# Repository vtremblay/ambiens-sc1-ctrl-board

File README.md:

# ambiens-sc1-ctrl-board

The Ambiens SC1 Control Board is the heart of a smart heated 3D printer chamber designed to create an optimal environment for 3D printing by precisely controlling temperature and air quality. It continuously monitors the air quality inside the chamber using two BME680 sensors to assess the Indoor Air Quality (IAQ). Depending on the IAQ levels, a PWM fan is activated, working in conjunction with a HEPA filter and activated charcoal filters to purify the air.

To maintain the ideal temperature for different printing materials, the chamber utilizes a generic 12V PTC heater (120W) paired with a fan. The system's safety is enhanced by a 100k NTC sensor embedded in the PTC heater to monitor its internal temperature, alongside a thermal fuse to prevent overheating by automatically cutting off the heater if temperatures exceed safe levels.

The control board is powered by an ATX PSU and interfaces with a Raspberry Pi 3B via I2C, offering a smart, modular solution for 3D printing enthusiasts looking to optimize their printing environment for quality and safety.

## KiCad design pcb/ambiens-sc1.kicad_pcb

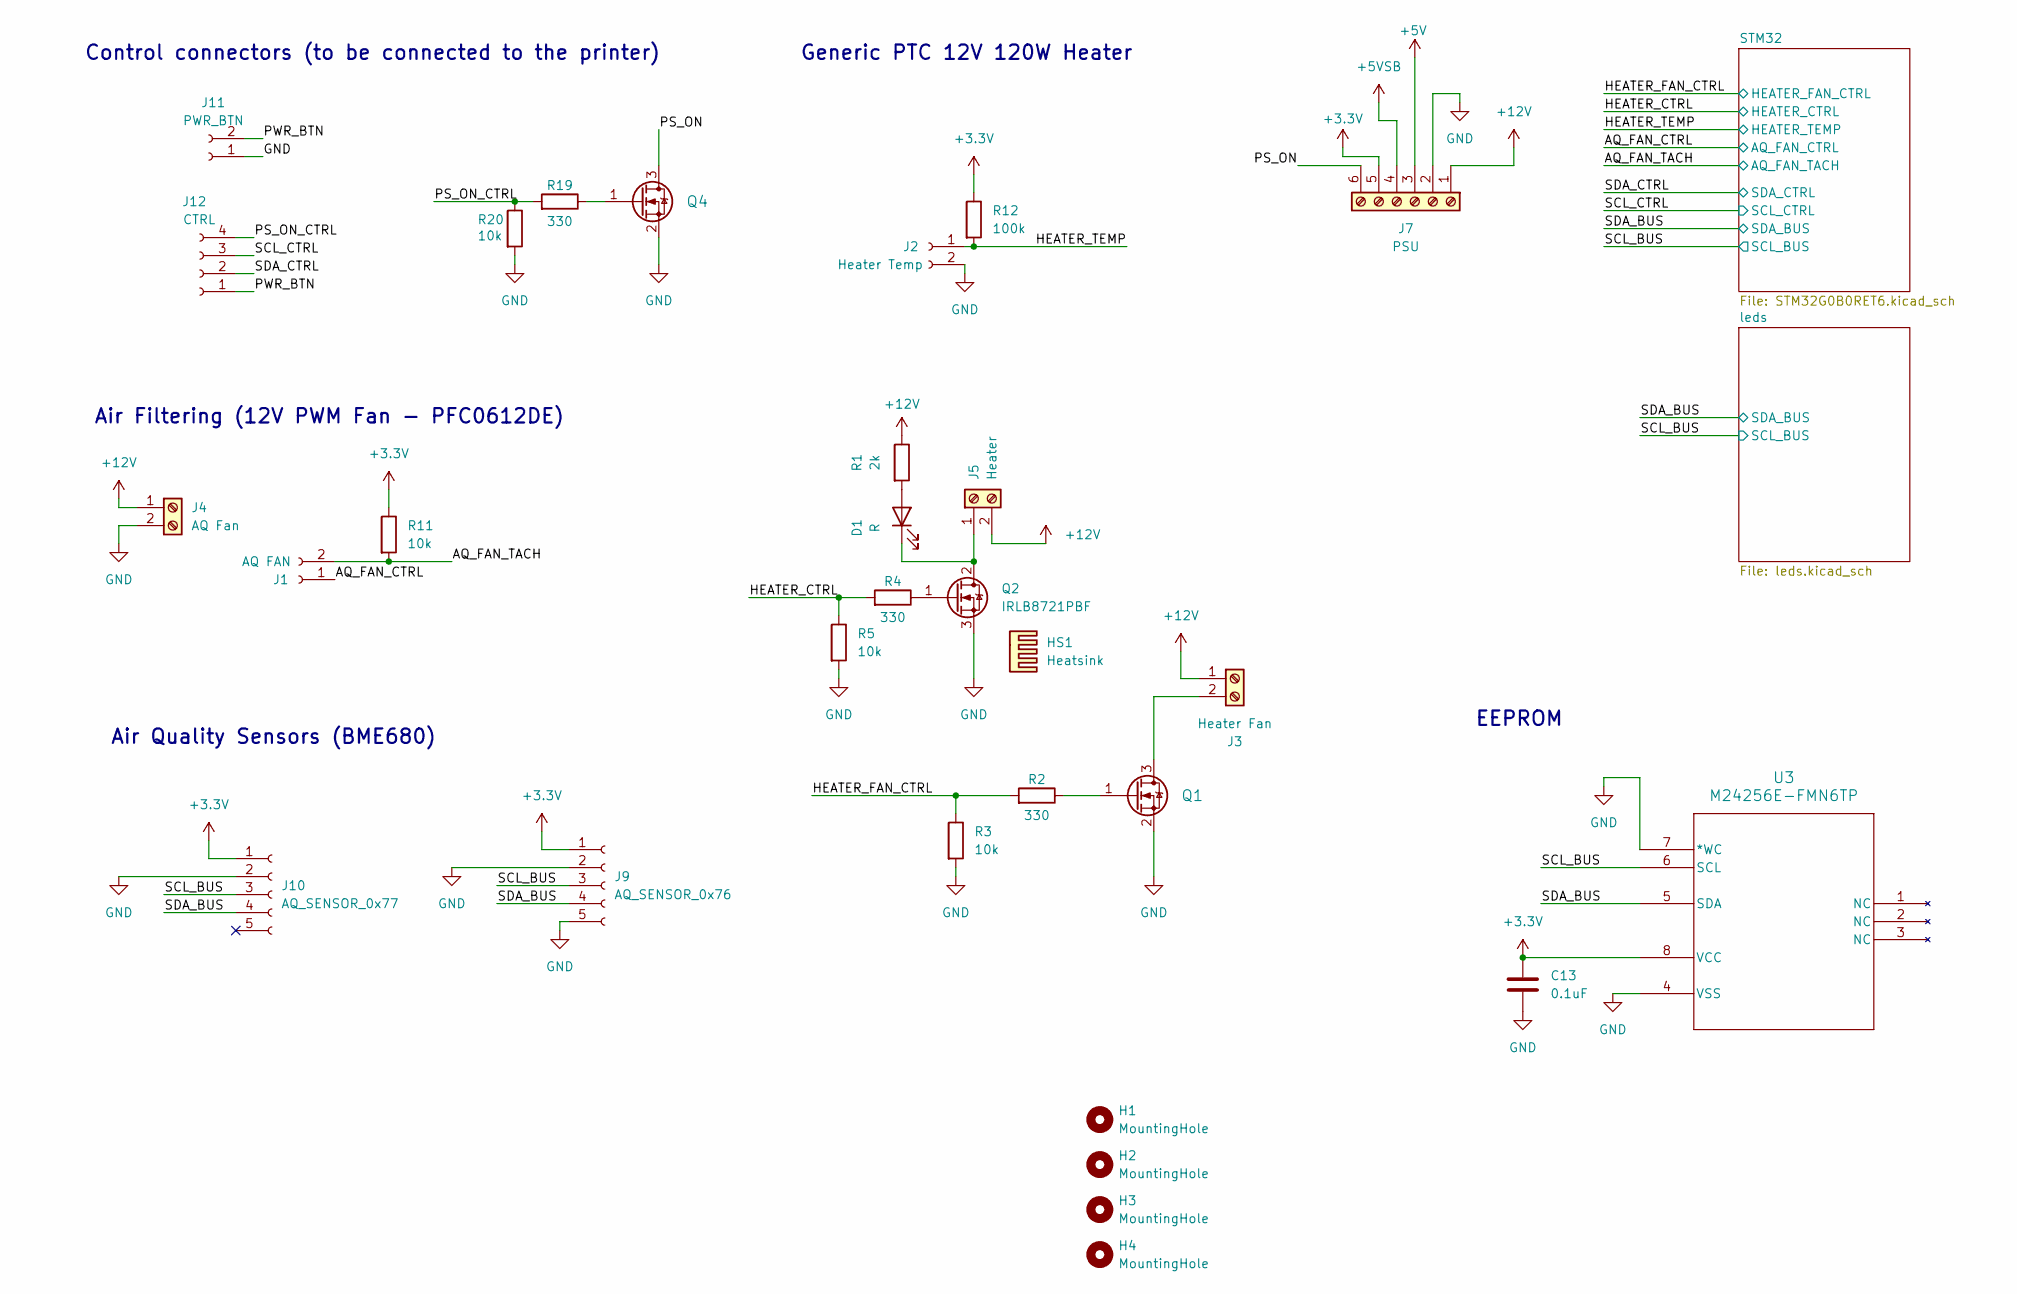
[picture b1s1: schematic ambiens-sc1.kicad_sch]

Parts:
C13: 0.1uF; C_0603_1608Metric
D1: R; LED_0805_2012Metric
H1, H2, H3, H4: MountingHole; MountingHole_3.2mm_M3
HS1: Heatsink; heatsink-15x10mm
J1: AQ FAN; JST_XH_B2B-XH-A_1x02_P2.50mm_Vertical
J2: Heater Temp; JST_XH_B2B-XH-A_1x02_P2.50mm_Vertical
J3: Heater Fan; TerminalBlock_Phoenix_MKDS-1,5-2_1x02_P5.00mm_Horizontal
J4: AQ Fan; TerminalBlock_Phoenix_MKDS-1,5-2_1x02_P5.00mm_Horizontal
J5: Heater; TerminalBlock_Phoenix_MKDS-1,5-2_1x02_P5.00mm_Horizontal
J7: PSU; TerminalBlock_Phoenix_MKDS-1,5-6-5.08_1x06_P5.08mm_Horizont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
J9: AQ_SENSOR_0x76; JST_XH_B5B-XH-A_1x05_P2.50mm_Vertical
J10: AQ_SENSOR_0x77; JST_XH_B5B-XH-A_1x05_P2.50mm_Vertical
J11: PWR_BTN; JST_XH_B2B-XH-A_1x02_P2.50mm_Vertical
J12: CTRL; JST_XH_B4B-XH-A_1x04_P2.50mm_Vertical
Q1, Q4: SI2302; SOT-23-3
Q2: IRLB8721PBF; TO-220-3_Vertical
R1: 2k; R_0805_2012Metric
R2, R4, R19: 330; R_0805_2012Metric
R3, R5, R11, R20: 10k; R_0805_2012Metric
R12: 100k; R_0805_2012Metric
U3: M24256E-FMN6TP; SO8N_4X5X1P27_STM

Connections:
+3.3V: C13.1, J7.5, J9.1, J10.1, R11.1, R12.1, U3.8 (VCC); also elsewhere on the board
+5V: J7.3; also elsewhere on the board
+5VSB: J7.4; also elsewhere on the board
+12V: J3.1, J4.1, J5.2, J7.1, R1.1; also elsewhere on the board
/AQ_FAN_CTRL: J1.1; also elsewhere on the board
/AQ_FAN_TACH: J1.2, R11.2; also elsewhere on the board
/HEATER_CTRL: R4.2, R5.1; also elsewhere on the board
/HEATER_FAN_CTRL: R2.2, R3.1; also elsewhere on the board
/HEATER_TEMP: J2.1, R12.2; also elsewhere on the board
/PS_ON: J7.6, Q4.3 (D)
/PS_ON_CTRL: J12.4, R19.2, R20.1
/PWR_BTN: J11.2, J12.1
/SCL_BUS: J9.3, J10.3, U3.6 (SCL); also elsewhere on the board
/SCL_CTRL: J12.3; also elsewhere on the board
/SDA_BUS: J9.4, J10.4, U3.5 (SDA); also elsewhere on the board
/SDA_CTRL: J12.2; also elsewhere on the board
GND: C13.2, J2.2, J4.2, J7.2, J9.2, J9.5, J10.2, J11.1, Q1.2 (S), Q2.3 (S), Q4.2 (S), R3.2, R5.2, R20.2, U3.4 (VSS), U3.7 (*WC); also elsewhere on the board
unnamed: D1.2 (A), R1.2
unnamed: D1.1 (K), J5.1, Q2.2 (D)
unnamed: J3.2, Q1.3 (D)
unnamed: Q1.1 (G), R2.1
unnamed: Q2.1 (G), R4.1
unnamed: Q4.1 (G), R19.1

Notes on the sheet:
Air Quality Sensors (BME680)
Generic PTC 12V 120W Heater
Control connectors (to be connected to the printer)
EEPROM
Air Filtering (12V PWM Fan - PFC0612DE)

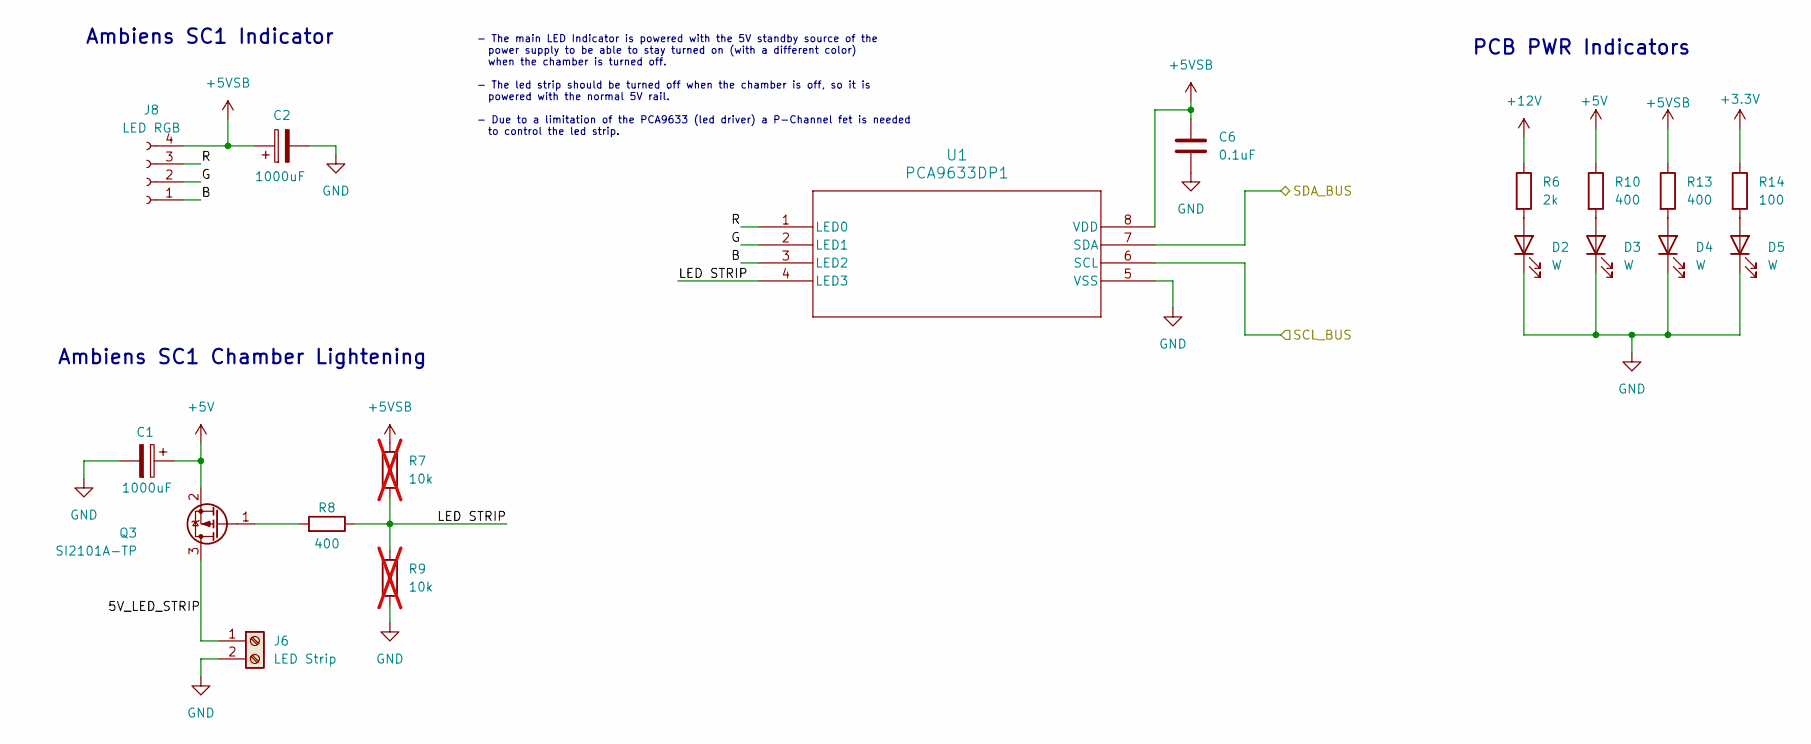
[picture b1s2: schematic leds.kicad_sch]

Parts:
C1, C2: 1000uF; CP_Radial_D10.0mm_P5.00mm
C6: 0.1uF; C_0603_1608Metric
D2, D3, D4, D5: W; LED_0805_2012Metric
J6: LED Strip; TerminalBlock_Phoenix_MKDS-1,5-2_1x02_P5.00mm_Horizontal
J8: LED RGB; JST_XH_B4B-XH-A_1x04_P2.50mm_Vertical
Q3: SI2101A-TP; SOT65P228X120-3N
R6: 2k; R_0805_2012Metric
R7, R9: 10k; R_0805_2012Metric; not fitted
R8, R10, R13: 400; R_0805_2012Metric
R14: 100; R_0805_2012Metric
U1: PCA9633DP1; SOT505-1_NXP

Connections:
+3.3V: R14.1; also elsewhere on the board
+5V: C1.1, Q3.2 (S), R10.1; also elsewhere on the board
+5VSB: C2.1, C6.1, J8.4, R7.1, R13.1, U1.8 (VDD); also elsewhere on the board
+12V: R6.1; also elsewhere on the board
/SCL_BUS: U1.6 (SCL); also elsewhere on the board
/SDA_BUS: U1.7 (SDA); also elsewhere on the board
/leds/5V_LED_STRIP: J6.1, Q3.3 (D)
/leds/B: J8.1, U1.3 (LED2)
/leds/G: J8.2, U1.2 (LED1)
/leds/LED STRIP: R7.2, R8.1, R9.1, U1.4 (LED3)
/leds/R: J8.3, U1.1 (LED0)
GND: C1.2, C2.2, C6.2, D2.1 (K), D3.1 (K), D4.1 (K), D5.1 (K), J6.2, R9.2, U1.5 (VSS); also elsewhere on the board
unnamed: D2.2 (A), R6.2
unnamed: D3.2 (A), R10.2
unnamed: D4.2 (A), R13.2
unnamed: D5.2 (A), R14.2
unnamed: Q3.1 (G), R8.2

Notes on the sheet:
PCB PWR Indicators
Ambiens SC1 Indicator
- The main LED Indicator is powered with the 5V standby source of the power supply to be able to stay turned on (with a different color) when the chamber is turned off. - The led strip should be turned off when the chamber is off, so it is powered with the normal 5V rail. - Due to a limitation of t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
Ambiens SC1 Chamber Lightening

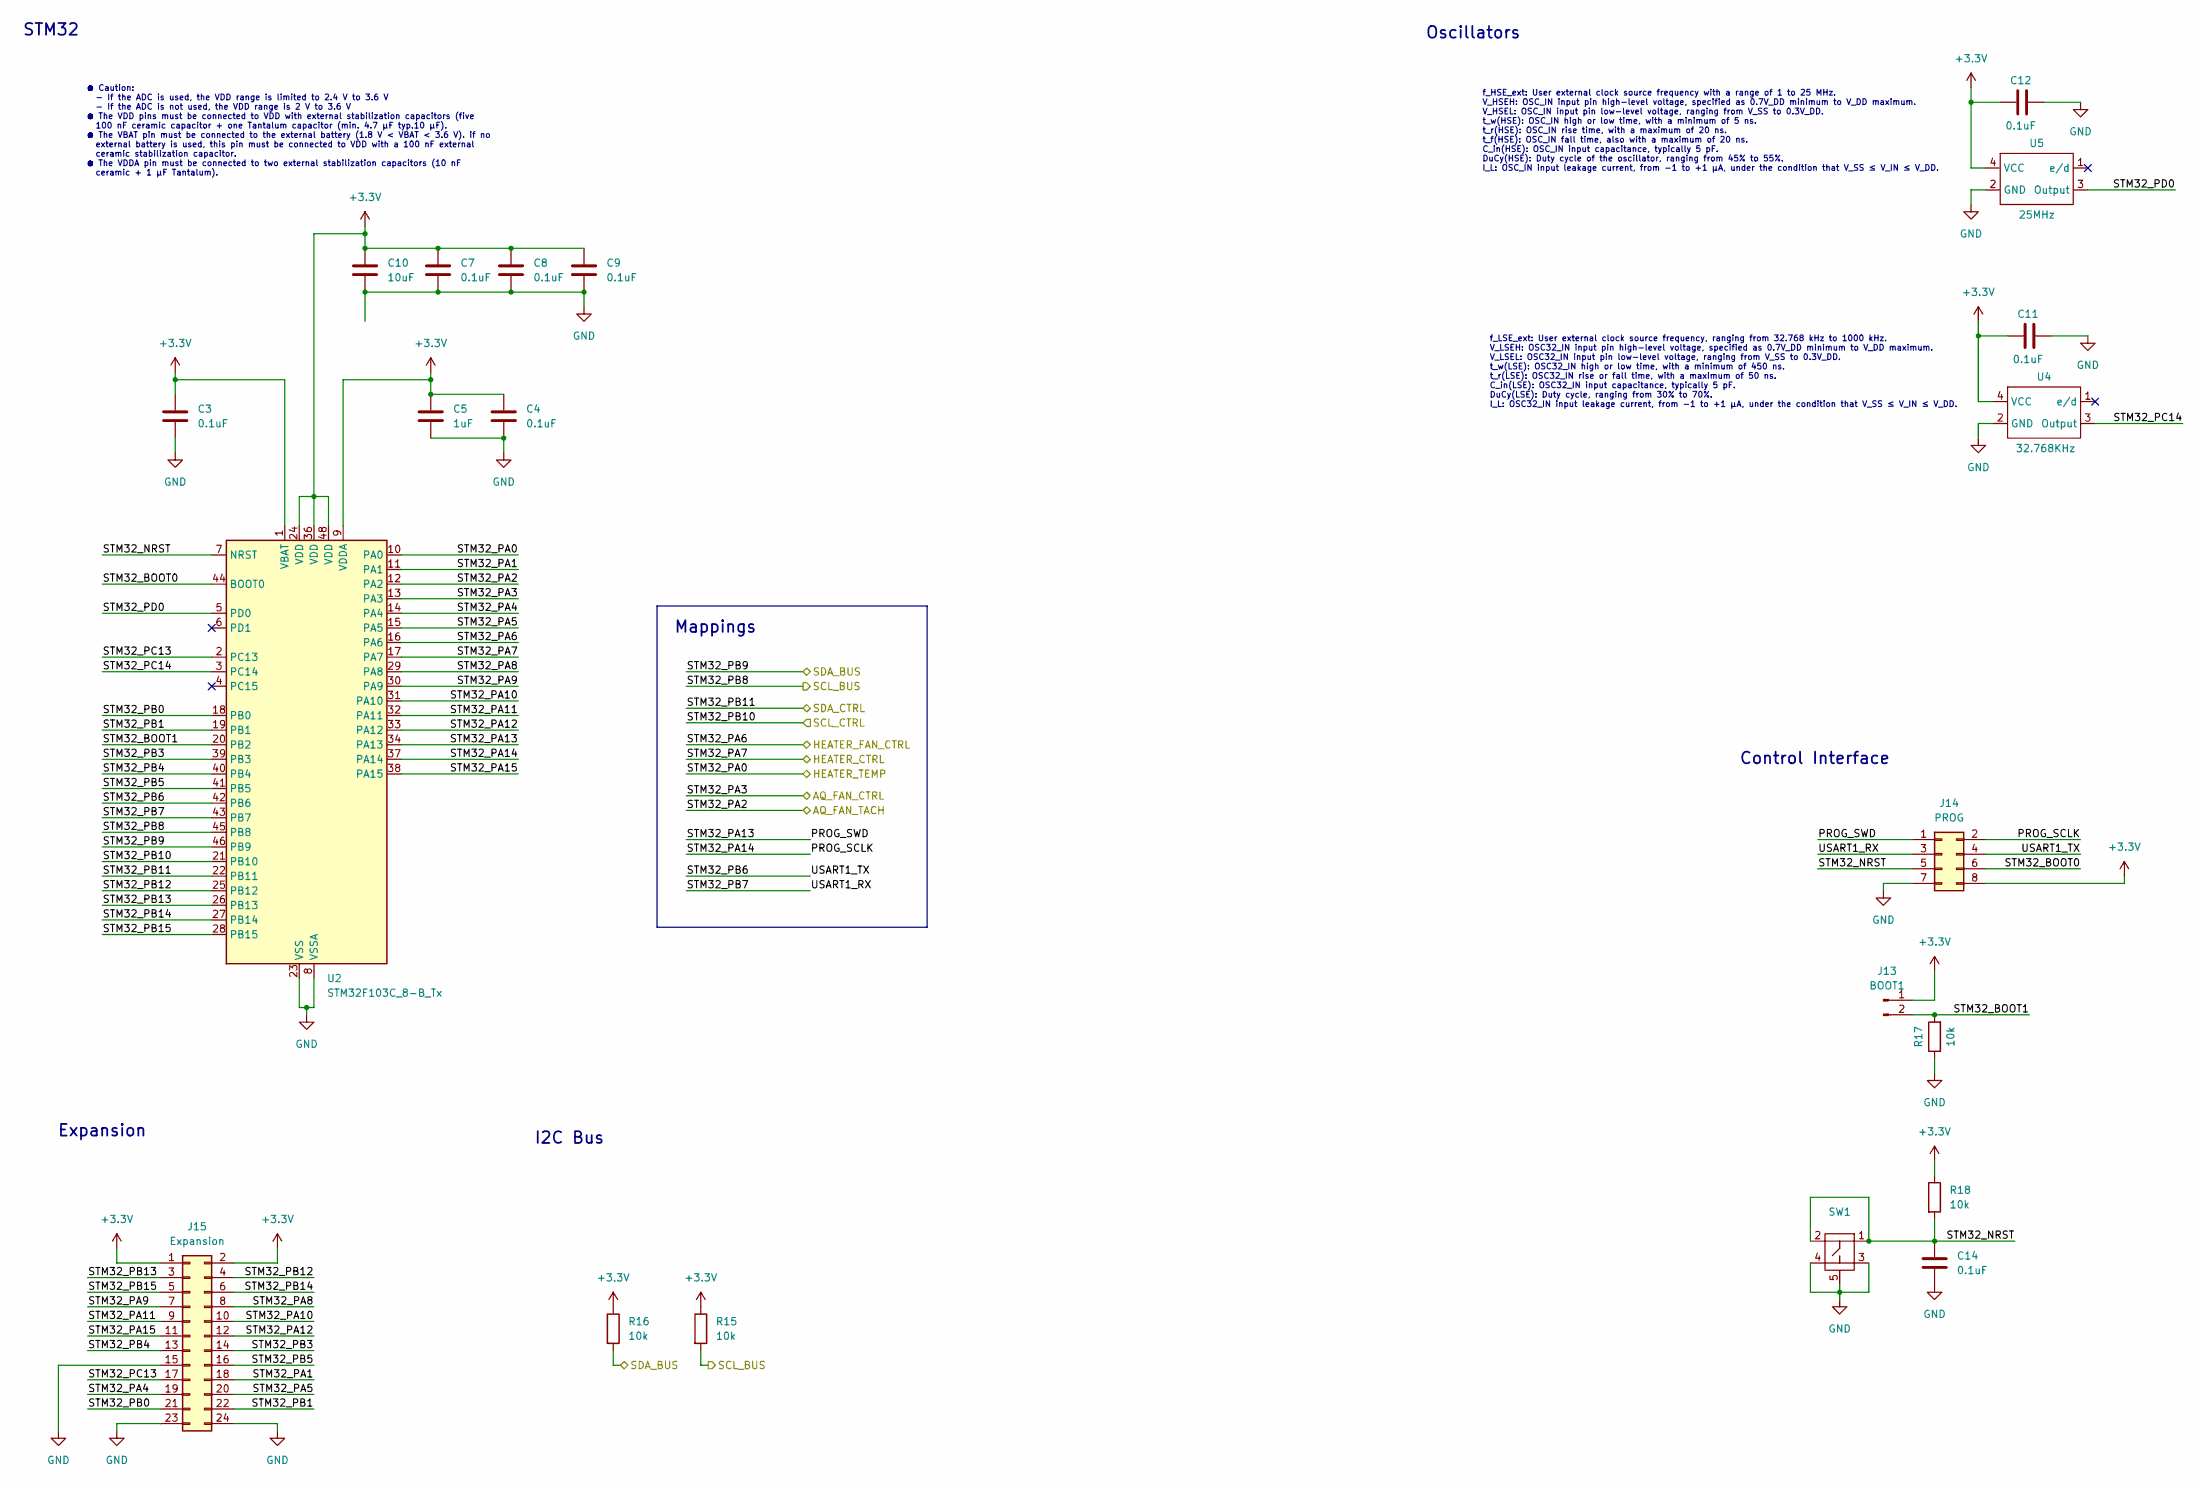
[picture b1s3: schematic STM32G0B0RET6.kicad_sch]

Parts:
C3, C4, C7, C8, C9, C11, C12, C14: 0.1uF; C_0603_1608Metric
C5: 1uF; C_0805_2012Metric
C10: 10uF; C_0805_2012Metric
J13: BOOT1; PinHeader_1x02_P2.54mm_Vertical
J14: PROG; PinHeader_2x04_P2.54mm_Vertical
J15: Expansion; PinHeader_2x12_P2.54mm_Vertical
R15, R16, R17, R18: 10k; R_0805_2012Metric
SW1: TS3315A
U2: STM32F103C_8-B_Tx; LQFP-48_7x7mm_P0.5mm
U4: 32.768KHz; SX3M32.768
U5: 25MHz; OT322525MJBA4SL

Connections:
+3.3V: C3.1, C4.1, C5.1, C7.1, C8.1, C9.1, C10.1, C11.1, C12.1, J13.1, J14.8, J15.1, J15.2, R15.1, R16.1, R18.1, U2.1 (VBAT), U2.9 (VDDA), U2.24 (VDD), U2.36 (VDD), U2.48 (VDD), U4.4 (VCC), U5.4 (VCC); also elsewhere on the board
/AQ_FAN_CTRL: U2.13 (PA3); also elsewhere on the board
/AQ_FAN_TACH: U2.12 (PA2); also elsewhere on the board
/HEATER_CTRL: U2.17 (PA7); also elsewhere on the board
/HEATER_FAN_CTRL: U2.16 (PA6); also elsewhere on the board
/HEATER_TEMP: U2.10 (PA0); also elsewhere on the board
/SCL_BUS: R15.2, U2.45 (PB8); also elsewhere on the board
/SCL_CTRL: U2.21 (PB10); also elsewhere on the board
/SDA_BUS: R16.2, U2.46 (PB9); also elsewhere on the board
/SDA_CTRL: U2.22 (PB11); also elsewhere on the board
/STM32/PROG_SCLK: J14.2, U2.37 (PA14)
/STM32/PROG_SWD: J14.1, U2.34 (PA13)
/STM32/STM32_BOOT0: J14.6, U2.44 (BOOT0)
/STM32/STM32_BOOT1: J13.2, R17.2, U2.20 (PB2)
/STM32/STM32_NRST: C14.1, J14.5, R18.2, SW1.1, SW1.2, U2.7 (NRST)
/STM32/STM32_PA1: J15.18, U2.11 (PA1)
/STM32/STM32_PA4: J15.19, U2.14 (PA4)
/STM32/STM32_PA5: J15.20, U2.15 (PA5)
/STM32/STM32_PA8: J15.8, U2.29 (PA8)
/STM32/STM32_PA9: J15.7, U2.30 (PA9)
/STM32/STM32_PA10: J15.10, U2.31 (PA10)
/STM32/STM32_PA11: J15.9, U2.32 (PA11)
/STM32/STM32_PA12: J15.12, U2.33 (PA12)
/STM32/STM32_PA15: J15.11, U2.38 (PA15)
/STM32/STM32_PB0: J15.21, U2.18 (PB0)
/STM32/STM32_PB1: J15.22, U2.19 (PB1)
/STM32/STM32_PB3: J15.14, U2.39 (PB3)
/STM32/STM32_PB4: J15.13, U2.40 (PB4)
/STM32/STM32_PB5: J15.16, U2.41 (PB5)
/STM32/STM32_PB6: J14.4, U2.42 (PB6)
/STM32/STM32_PB7: J14.3, U2.43 (PB7)
/STM32/STM32_PB12: J15.4, U2.25 (PB12)
/STM32/STM32_PB13: J15.3, U2.26 (PB13)
/STM32/STM32_PB14: J15.6, U2.27 (PB14)
/STM32/STM32_PB15: J15.5, U2.28 (PB15)
/STM32/STM32_PC13: J15.17, U2.2 (PC13)
/STM32/STM32_PC14: U2.3 (PC14), U4.3 (Output)
/STM32/STM32_PD0: U2.5 (PD0), U5.3 (Output)
GND: C3.2, C4.2, C5.2, C7.2, C8.2, C9.2, C10.2, C11.2, C12.2, C14.2, J14.7, J15.15, J15.23, J15.24, R17.1, SW1.3, SW1.4, SW1.5, U2.8 (VSSA), U2.23 (VSS), U2.35 (VSS), U2.47 (VSS), U4.2 (GND), U5.2 (GND); also elsewhere on the board

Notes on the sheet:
● Caution: - If the ADC is used, the VDD range is limited to 2.4 V to 3.6 V - If the ADC is not used, the VDD range is 2 V to 3.6 V ● The VDD pins must be connected to VDD with external stabilization capacitors (five 100 nF ceramic capacitor + one Tantalum capacitor (min. 4.7 µF typ.10 µF). ● The V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
f_HSE_ext: User external clock source frequency with a range of 1 to 25 MHz. V_HSEH: OSC_IN input pin high-level voltage, specified as 0.7V_DD minimum to V_DD maximum. V_HSEL: OSC_IN input pin low-level voltage, ranging from V_SS to 0.3V_DD. t_w(HSE): OSC_IN high or low time, with a minimum of 5 ns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
Expansion
Oscillators
Control Interface
STM32
I2C Bus
Mappings
f_LSE_ext: User external clock source frequency, ranging from 32.768 kHz to 1000 kHz. V_LSEH: OSC32_IN input pin high-level voltage, specified as 0.7V_DD minimum to V_DD maximum. V_LSEL: OSC32_IN input pin low-level voltage, ranging from V_SS to 0.3V_DD. t_w(LSE): OSC32_IN high or low time, with a 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

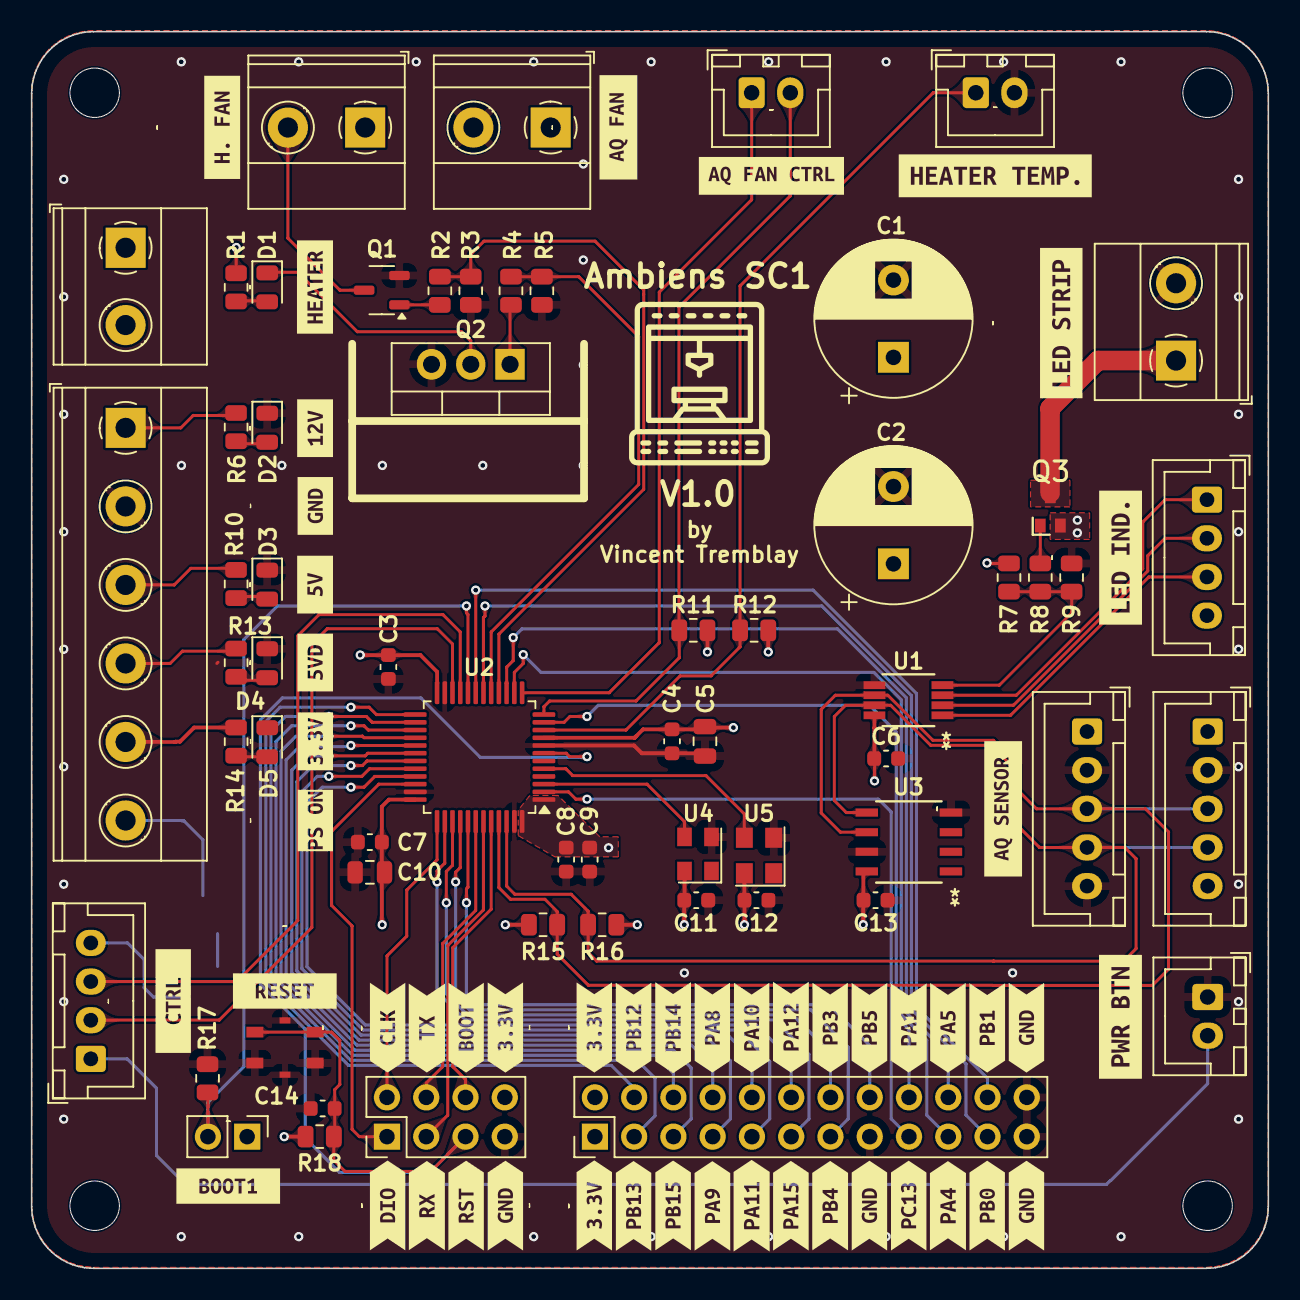
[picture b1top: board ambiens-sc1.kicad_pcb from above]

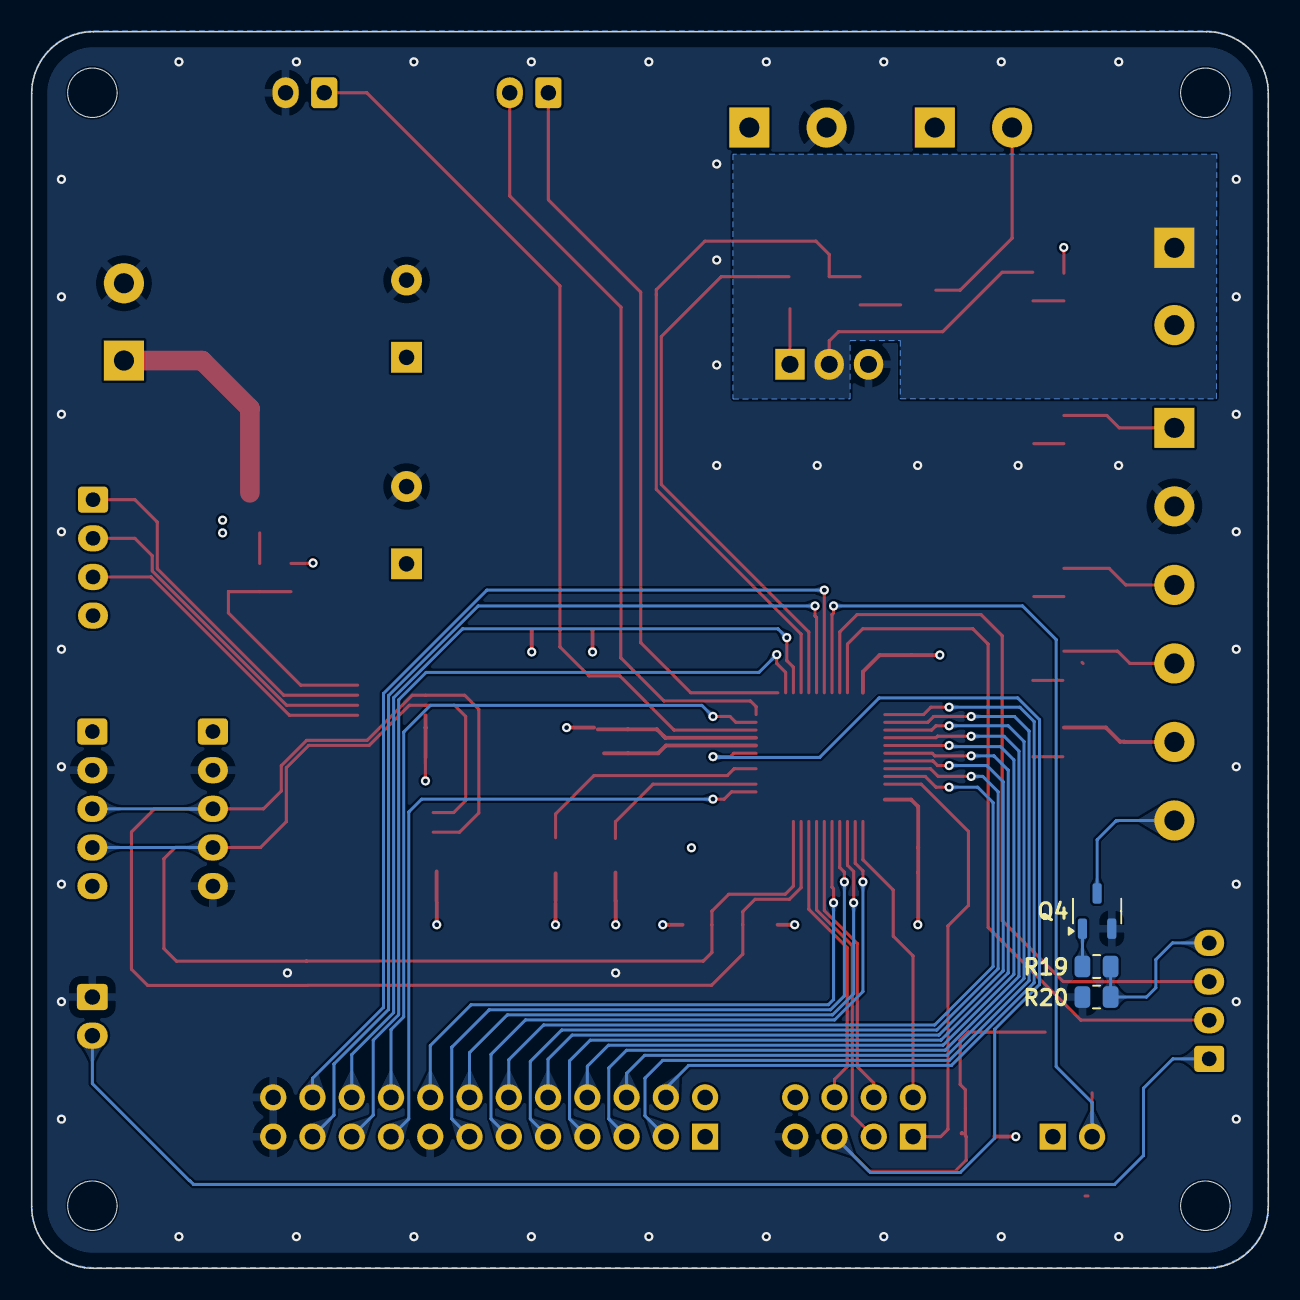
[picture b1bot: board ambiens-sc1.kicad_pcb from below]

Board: 4 copper layers, 80.0 x 80.0 mm, 119 parts (3 on the bottom side), 61 nets.

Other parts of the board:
kibuzzard-2: G***; kibuzzard-660B36FB
kibuzzard-3: G***; kibuzzard-660B379A
kibuzzard-4: G***; kibuzzard-660B3822
kibuzzard-5: G***; kibuzzard-660B3897
kibuzzard-6: G***; kibuzzard-660B3677
kibuzzard-7: G***; kibuzzard-660B3911
kibuzzard-8: G***; kibuzzard-660B3380
kibuzzard-9: G***; kibuzzard-660B338A
kibuzzard-10: G***; kibuzzard-660B3947
kibuzzard-11: G***; kibuzzard-660B3393
kibuzzard-12: G***; kibuzzard-660B339B
kibuzzard-13: G***; kibuzzard-660B33A2
kibuzzard-14: G***; kibuzzard-660B3A88
kibuzzard-15: G***; kibuzzard-660B3361
kibuzzard-16: G***; kibuzzard-660B3C6C
kibuzzard-17: G***; kibuzzard-660B3B0F
kibuzzard-18: G***; kibuzzard-660D448F
kibuzzard-19: G***; kibuzzard-66046388
kibuzzard-20: G***; kibuzzard-660AE3B8
kibuzzard-21: G***; kibuzzard-66072EC4
kibuzzard-22: G***; kibuzzard-660AD604
kibuzzard-23: G***; kibuzzard-6604645B
kibuzzard-24: G***; kibuzzard-66072F4D
kibuzzard-25: G***; kibuzzard-660B1E5B
kibuzzard-26: G***; kibuzzard-66072F6D
kibuzzard-27: G***; kibuzzard-66072F74
kibuzzard-28: G***; kibuzzard-66072F85
kibuzzard-29: G***; kibuzzard-660463B7
kibuzzard-30: G***; kibuzzard-66072F98
kibuzzard-31: G***; kibuzzard-660B1183
kibuzzard-32: G***; kibuzzard-660B0DE1
kibuzzard-33: G***; kibuzzard-660B118A
kibuzzard-34: G***; kibuzzard-660AE448
kibuzzard-35: G***; kibuzzard-660B3B39
kibuzzard-37: G***; kibuzzard-66045831
kibuzzard-38: G***; kibuzzard-66072EDA
kibuzzard-39: G***; kibuzzard-660AE44F
kibuzzard-40: G***; kibuzzard-660AD65A
kibuzzard-41: G***; kibuzzard-66046448
kibuzzard-42: G***; kibuzzard-660B0F13
kibuzzard-43: G***; kibuzzard-660B1175
kibuzzard-44: G***; kibuzzard-660B0DE8
kibuzzard-45: G***; kibuzzard-66072EED
kibuzzard-46: G***; kibuzzard-66072EF6
kibuzzard-47: G***; kibuzzard-66072EFF
kibuzzard-48: G***; kibuzzard-660B117C
kibuzzard-49: G***; kibuzzard-66072F2C
kibuzzard-50: G***; kibuzzard-66072ED0
kibuzzard-51: G***; kibuzzard-66072EE1
kibuzzard-6634D528: G***; kibuzzard-6634D528

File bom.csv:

"Reference","Value","Datasheet","Footprint","Qty","DNP","Description"
"C1,C2","1000uF","https://industrial.panasonic.com/cdbs/www-data/pdf/RDF0000/A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","Capacitor_THT:CP_Radial_D10.0mm_P5.00mm","2","","EEUFS1V102L"
"C3,C4,C6,C7,C8,C9,C11,C12,C13,C14","0.1uF","~","Capacitor_SMD:C_0603_1608Metric","10","","Unpolarized capacitor"
"C5","1uF","~","Capacitor_SMD:C_0805_2012Metric","1","","Unpolarized capacitor"
"C10","10uF","~","Capacitor_SMD:C_0805_2012Metric","1","","Unpolarized capacitor"
"D1","R","~","LED_SMD:LED_0805_2012Metric","1","","Light emitting diode"
"D2,D3,D4,D5","W","~","LED_SMD:LED_0805_2012Metric","4","","Light emitting diode"
"H1,H2,H3,H4","MountingHole","~","MountingHole:MountingHole_3.2mm_M3","4","","Mounting Hole without connection"
"HS1","Heatsink","~","custom:heatsink-15x10mm","1","","Heatsink"
"J1,J2,J11","","~","Connector_JST:JST_XH_B2B-XH-A_1x02_P2.50mm_Vertical","3","","Generic connector, single row, 01x02, script generated"
"J3,J4,J5,J6","","~","TerminalBlock_Phoenix:TerminalBlock_Phoenix_MKDS-1,5-2_1x02_P5.00mm_Horizontal","4","","DB128V-5.08-2P-GN-S"
"J7","","~","TerminalBlock_Phoenix:TerminalBlock_Phoenix_MKDS-1,5-6-5.08_1x06_P5.08mm_Horizontal","1","","DORABO DB128V-5.08-6P-GN-S "
"J8,J12","","~","Connector_JST:JST_XH_B4B-XH-A_1x04_P2.50mm_Vertical","2","","Generic connector, single row, 01x04, script generated"
"J9,J10","","~","Connector_JST:JST_XH_B5B-XH-A_1x05_P2.50mm_Vertical","2","","Generic connector, single row, 01x05, script generated"
"J13","","~","Connector_PinHeader_2.54mm:PinHeader_1x02_P2.54mm_Vertical","1","","Generic connector, single row, 01x02, script generated"
"J14","","~","Connector_PinHeader_2.54mm:PinHeader_2x04_P2.54mm_Vertical","1","","Generic connector, double row, 02x04, odd/even pin numbering scheme (row 1 odd numbers, row 2 even numbers), script generated (kicad-library-utils/schlib/autogen/connector/)"
"J15","","~","Connector_PinHeader_2.54mm:PinHeader_2x12_P2.54mm_Vertical","1","","Generic connector, double row, 02x12, odd/even pin numbering scheme (row 1 odd numbers, row 2 even numbers), script generated (kicad-library-utils/schlib/autogen/connector/)"
"Q1,Q4","SI2302","~","Package_TO_SOT_SMD:SOT-23-3","2","","N-MOSFET transistor, gate/source/drain"
"Q2","IRLB8721PBF","http://www.infineon.com/dgdl/irlb8721pbf.pdf?fileId=5546d462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","Package_TO_SOT_THT:TO-220-3_Vertical","1","","62A Id, 30V Vds, 8.7 mOhm Rds, N-Channel HEXFET Power MOSFET, TO-220"
"Q3","SI2101A-TP","~","si2120a-tp:SOT65P228X120-3N","1","","P-MOSFET transistor, gate/source/drain"
"R1,R6","2k","~","Resistor_SMD:R_0805_2012Metric","2","","Resistor"
"R2,R4,R19","330","~","Resistor_SMD:R_0805_2012Metric","3","","Resistor"
"R3,R5,R11,R15,R16,R17,R18,R20","10k","~","Resistor_SMD:R_0805_2012Metric","8","","Resistor"
"R7,R9","10k","~","Resistor_SMD:R_0805_2012Metric","2","DNP","Resistor"
"R8,R10,R13","400","~","Resistor_SMD:R_0805_2012Metric","3","","Resistor"
"R12","100k","~","Resistor_SMD:R_0805_2012Metric","1","","Resistor"
"R14","100","~","Resistor_SMD:R_0805_2012Metric","1","","Resistor"
"SW1","~","","Button_Switch_SMD:TS3315A","1","",""
"U1","PCA9633DP1","PCA9633DP1","PCA9633DP1:SOT505-1_NXP","1","",""
"U2","STM32F103C_8-B_Tx","https://www.st.com/resource/en/datasheet/stm32f103c8.pdf","Package_QFP:LQFP-48_7x7mm_P0.5mm","1","","STMicroelectronics Arm Cortex-M3 MCU, 64-128KB flash, 20KB RAM, 72 MHz, 2.0-3.6V, 37 GPIO, LQFP48"
"U3","M24256E-FMN6TP","M24256E-FMN6TP","M24256E-FMN6TP:SO8N_4X5X1P27_STM","1","",""
"U4","32.768KHz","https://www.lcsc.com/datasheet/lcsc_datasheet_2110091030_She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","Oscillator:SX3M32.768","1","","SX3M32.768KM20F30TNN"
"U5","25MHz","https://www.lcsc.com/datasheet/lcsc_datasheet_2304140030_YXC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","Oscillator:OT322525MJBA4SL","1","","OT322525MJBA4SL"

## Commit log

2024-04-03 Initial
2024-04-03 readme
2024-04-04 gerbers
2024-04-04 small fixes
2024-05-03 Fix red led + label typo
